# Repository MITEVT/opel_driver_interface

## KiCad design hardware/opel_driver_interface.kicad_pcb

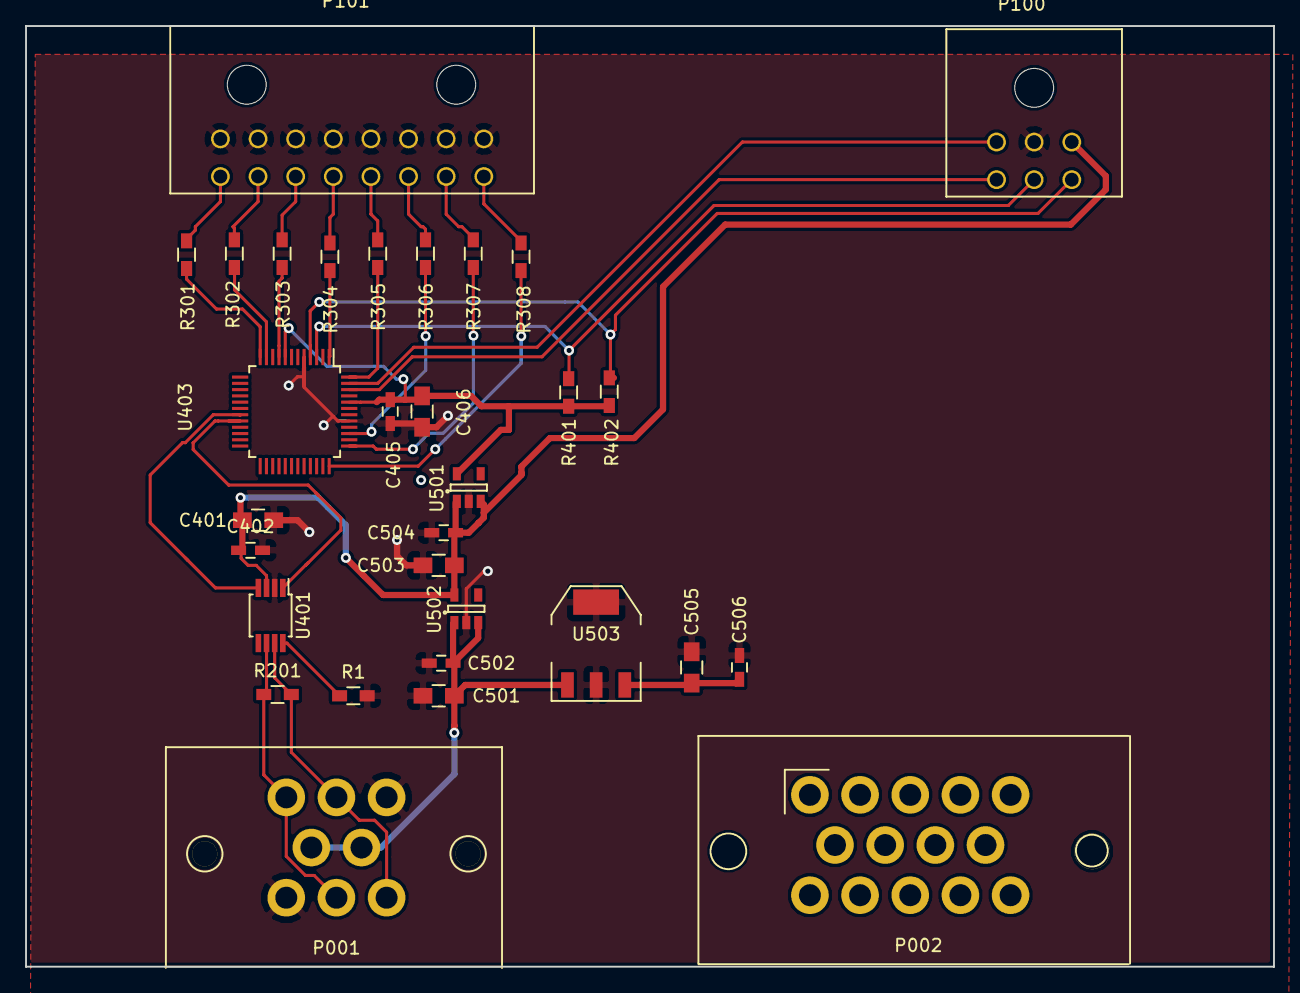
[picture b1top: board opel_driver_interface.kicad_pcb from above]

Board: 2 copper layers, 99.5 x 75.0 mm, 31 parts (0 on the bottom side), 30 nets.

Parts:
C401, C406: 10uF; C_0805_HandSoldering
C402, C405: 0.1uF; C_0603_HandSoldering
C501, C503, C505: 10μ; C_0805_HandSoldering
C502, C504, C506: .1μ; C_0603_HandSoldering
P001: CANCONNECTOR; 776280-1
P002: CONN_01X14; 776267-1
P100: ISP; Connector_Microfit3_Header_02x03_Angled_43045-060x
P101: DEBUG_LED; Connector_Microfit3_Header_02x08_Angled_43045-160x
R1: 20k; R_0603_HandSoldering
R201: R; R_0603_HandSoldering
R301, R302, R303, R304, R305, R306, R307, R308: 100; R_0603_HandSoldering
R401, R402: 10k; R_0603_HandSoldering
U401: MCP2551-I/SN; MSOP-8_3x3mm_Pitch0.65mm
U403: LPC11C14; LQFP-48_7x7mm_Pitch0.5mm
U501: MCP1755-33; SOT-23-5
U502: MCP1755-5; SOT-23-5
U503: Zsr1000gta; SOT-223

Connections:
+3V3: C405.1, C406.1, R401.1, R402.1, U403.8, U403.44, U501.5
+5V: C401.1, C402.1, C503.1, C504.1, P100.3, U401.3, U501.1, U501.3, U502.5
+12V: C501.2, C502.1, P001.4, P001.5, U502.1, U502.3, U503.1
/BACK_PANEL/CANH: P001.2, P001.8, R201.2, U401.7
/BACK_PANEL/CANL: P001.1, P001.7, R201.1, U401.6
/FRONT_PANEL/LED0: R301.1, U403.12
/FRONT_PANEL/LED1: R302.2, U403.11
/FRONT_PANEL/LED2: R303.2, U403.9
/FRONT_PANEL/LED3: R304.1, U403.1
/FRONT_PANEL/LED4: R305.2, U403.48
/FRONT_PANEL/LED5: R306.1, U403.39
/FRONT_PANEL/LED6: R307.2, U403.37
/FRONT_PANEL/LED7: R308.1, U403.36
/FRONT_PANEL/MCU_PROG_N: P100.6, R402.2, U403.4
/FRONT_PANEL/MCU_RESET_N: P100.5, R401.2, U403.3
/FRONT_PANEL/RXD: P100.4, U403.46
/FRONT_PANEL/TXD: P100.1, U403.47
/Micro_Controller/CAN_RXD: U401.4, U403.19
/Micro_Controller/CAN_TXD: U401.1, U403.20
GND: C401.2, C402.2, C405.2, C406.2, C501.1, C502.2, C503.2, C504.2, C505.1, C506.1, P001.3, P001.6, P100.2, P101.1, P101.2, P101.3, P101.4, P101.5, P101.6, P101.7, P101.8, R1.2, U401.2, U403.5, U403.41, U501.2, U502.2, U503.2, U503.4
unnamed: P101.9, R301.2
unnamed: P101.10, R302.1
unnamed: P101.11, R303.1
unnamed: P101.12, R304.2
unnamed: P101.13, R305.1
unnamed: P101.14, R306.2
unnamed: P101.15, R307.1
unnamed: P101.16, R308.2
unnamed: R1.1, U401.8
VCC: C505.2, C506.2, U503.3

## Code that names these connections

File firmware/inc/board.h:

#ifndef __BOARD_H_
#define __BOARD_H_

#include "chip.h"
#include "util.h"
#include <string.h>

// -------------------------------------------------------------
// Global Variables

extern const uint32_t OscRateIn;
volatile uint32_t msTicks; 						// Running count of milliseconds since start

// -------------------------------------------------------------
// Configuration Macros


// -------------------------------------------------------------
// Pin Descriptions

#define LED0_PORT 2
#define LED0_PIN 5

#define LED1_PORT 0
#define LED1_PIN 6

#define LED2_PORT 0
#define LED2_PIN 7

#define LED3_PORT 2
#define LED3_PIN 9

#define UART_RX_PORT 1
#define UART_RX_PIN 6
#define UART_RX_IOCON IOCON_PIO1_6

#define UART_TX_PORT 1
#define UART_TX_PIN 7
#define UART_TX_IOCON IOCON_PIO1_7

// -------------------------------------------------------------
// Computed Macros

#define LED0 LED0_PORT, LED0_PIN
#define LED1 LED1_PORT, LED1_PIN
#define LED2 LED2_PORT, LED2_PIN
#define LED3 LED3_PORT, LED3_PIN

#define UART_RX UART_RX_PORT, UART_RX_PIN
#define UART_TX UART_TX_PORT, UART_TX_PIN

#define Board_LED_On(led) Chip_GPIO_SetPinState(LPC_GPIO, led, true)
#define Board_LED_Off(led) Chip_GPIO_SetPinState(LPC_GPIO, led, false)

// -------------------------------------------------------------
// Board Level Function Prototypes

int8_t Board_SysTick_Init(void);

void Board_LEDs_Init(void);

void Board_UART_Init(uint32_t baudrate);

/**
 * Transmit the given string through the UART peripheral (blocking)
 *
 * @param str pointer to string to transmit
 * @note	This function will send or place all bytes into the transmit
 *			FIFO. This function will block until the last bytes are in the FIFO.
 */
void Board_UART_Print(const char *str);

/**
 * Transmit a string through the UART peripheral and append a newline and a linefeed character (blocking)
 *
 * @param str pointer to string to transmit
 * @note	This function will send or place all bytes into the transmit
 *			FIFO. This function will block until the last bytes are in the FIFO.
 */
void Board_UART_Println(const char *str);

/**
 * Transmit a string containing a number through the UART peripheral (blocking)
 *
 * @param num number to print
 * @param base number base
 * @param crlf append carraige return and line feed
 */
void Board_UART_PrintNum(const int num, uint8_t base, bool crlf);

/**
 * Transmit a byte array through the UART peripheral (blocking)
 *
 * @param	data		: Pointer to data to transmit
 * @param	num_bytes	: Number of bytes to transmit
 * @note	This function will send or place all bytes into the transmit
 *			FIFO. This function will block until the last bytes are in the FIFO.
 */
void Board_UART_SendBlocking(const void *data, uint8_t num_bytes);

/**
 * Read data through the UART peripheral (non-blocking)
 *
 * @param	data		: Pointer to bytes array to fill
 * @param	num_bytes	: Size of the passed data array
 * @return	The actual number of bytes read
 * @note	This function reads data from the receive FIFO until either
 *			all the data has been read or the passed buffer is completely full.
 *			This function will not block. This function ignores errors.
 */
int8_t Board_UART_Read(void *data, uint8_t num_bytes);

void Board_CAN_Init(uint32_t baudrate, void (*rx_callback)(uint8_t), void (*tx_callback)(uint8_t), void (*error_callback)(uint32_t));


#endif

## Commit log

2015-09-19 Initial Tmeplate Commit
2015-09-19 [template] add template for schematics
2015-09-21 Added C gitignore
2015-09-21 Fixed gitignore
2015-09-21 Cleaned up binaries
2015-09-21 Moved over external accessing functions to board file and trting out new test-before-send scheme
2015-09-21 Added README
2015-10-10 cleand repo and removed su files
2015-10-10 Fixed Comments
2015-10-10 Removed Errors
2015-10-24 Made some updates
2015-11-07 add state diagram
2015-11-07 move state diagram
2015-11-07 add new states
2015-11-07 Updating new types.h file
2015-11-07 finish
2015-11-07 Updated types.h
2015-11-07 changed the to da
2015-11-07 replace tabs with spaces
2015-11-14 Added a BLINKER_OFF in the turn_blinker enum
2015-11-14 Added pointers and added blinker struct and headlight struct
2015-11-14 Changed uint8_t switch1 to bool switch1
2015-11-14 Added accessories.c
2015-11-14 Added AccStep, and added variable names to DSM_Step
2015-11-14 Added dsm.c
2015-11-19 changed the inputs to the substate machine
2015-11-19 updated dsm state machine
2015-11-19 Finished half of the code
2015-11-19 added a bit more
2015-11-19 remove swp
2015-11-19 added heartbeat comment
2015-11-19 added init.h
2015-11-19 updated init.c
2015-11-21 fix types.h errors
2015-11-21 fix mode_mode_init
2015-11-21 change fn sigs
2015-11-21 not track vim shit
2015-11-21 progress
2015-11-21 finish accessories
2015-12-05 completed the helper functions
2015-12-05 completed the functions
2015-12-05 created util.h
2015-12-07 changed util.h to DIutil.h
2015-12-07 changed util.c to DIutil.c
2015-12-09 remove util.c
2015-12-09 rename di util
2015-12-09 Actually removed util.h
2015-12-09 changed the name to di_util.h
2015-12-10 added frequencies.h
2015-12-10 added ERROR_HEARTBEAT_LOST
2015-12-10 completed check_validity function
2015-12-10 update accessories fill it in
2015-12-10 added stdint.h
2015-12-10 finish error handling
2015-12-10 changes happened
2015-12-20 fill in main.c with main logic: process input frameworks, error handling, step through DSM, and output
2015-12-20 remove fail state fsm
2015-12-20 add skeletons for sub-FSMs
2016-01-09 updated input struct
2016-01-11 updated the accessories.c code and fixed logical errors
2016-01-11 updated dsm.c
2016-01-11 updated code
2016-01-12 finished init.c, added a counter variable to STATE_T, initialized variables in dsm.c
2016-01-13 inserted the logic for requests and made sure that Shutdown mode only has OFF requests
2016-01-15 removed TODO comment from init.c
2016-01-15 changed last 'else if' statements to 'else' statements at the end of every keymode block
2016-01-15 filled out the output stuff for shutdown.c
2016-01-15 set shutdown.c's acc_out to 'turn_all_off()'
2016-01-15 allowed drive_mode to be 'aux' or 'shutdown_impending'
2016-01-15 changed direction pointer into reg variable ('DRIVE_DIRECTION is an enum, not a struct')
2016-01-15 added comment below the TODO
2016-01-15 added types.h, and finished UART logic for printing out current DSM mode. Also made progress on UART logic on printing out input information
2016-01-16 changed keymodes from pointer to variable (for consistency)
2016-01-16 Finished TODO: for printing out accessory inputs
2016-01-16 added drive direction to States
2016-01-16 implemented direction switching when velocity != 0 and shutdown logic when velocity != 0
2016-01-20 fixed compilation error: OUTPUT_MESSAGES -> OUTPUT_MESSAGES_T
2016-01-20 pushed the pesky Drive direction T enum above everything else
2016-01-20 pushed the out_messages declaration above if else statement
2016-01-20 pushed out_messages delcaration above if else statement
2016-01-22 add types.h
2016-01-22 finish basic util and tests
2016-01-23 finish util processing
2016-01-27 add init outline
2016-01-29 add docs
2016-01-29 added tests of InitStep()
2016-01-30 Fixed documentation problem
    There needs to be two asterisks in the first line of the comment. See commit changes for better detail
2016-01-30 fixed outline and ran it through Eric
2016-01-30 fixed up init psuedocode
2016-01-30 init'd rasp_pi bool to false
2016-01-30 add ui status to inputs heartbeat type
2016-01-30 progress init state machine, add error to types.h
2016-01-30 update types error
2016-01-30 completed a new function (yay)
2016-01-30 updated tests
2016-01-30 finish init.c
2016-02-02 almost working init state machine code
2016-02-03 finish init state machine wahoooo
2016-02-03 add shutdown state; fix init cleanup bug
2016-02-06 fixed function description
2016-02-06 added details and functions to header file
2016-02-06 cleaned up setup
2016-02-06 added DI_NONE to DI_IGNITION
2016-02-06 added DRIVE_NEUTRAL to DRIVE_DIRECTION
2016-02-06 implemented initialize functions
2016-02-06 switched DI_FORWARD to DI_NEUTRAL
2016-02-06 completed asserts for statuses (the TODO) and completed initialize_state() test
2016-02-06 finish shutdown normal state !!!
2016-02-06 add can spec constants
2016-02-10 added units to velocity
2016-02-10 rm'd #include tests.h because it was causing compilation errors and refactored di_util.c to accomodate change from velocity -> velocity_rpm
2016-02-11 cleaned up test folder so that 'make test' compiles! we get A LOT of warnings though
2016-02-13 created test_shutdown_normal.c
2016-02-13 made sure 'make' compiled successfully (sorry for pushing broken code)
2016-02-20 added new ERROR Types, added functions to check Brake value and check velocity_rpm range
2016-02-20 fixed compilation errors
2016-02-20 added brake and throttle value range checks
2016-02-20 add charge design doc
2016-02-20 added function to test to di_util
2016-02-20 added skeleton of charge.c
2016-02-20 added RUN_TEST_GROUP(INIT__TESTS)
2016-02-20 tests pass!! OMG
2016-02-20 working running test file for init.c too!
2016-02-20 yay, everything but the test_init.c runs without compilation errors!
2016-02-20 finish init charge sequence
2016-02-20 add todo with brusa tests
2016-02-21 fix seg fault for init tests
2016-02-21 clean up init tests; tests pass wahoo
2016-03-05 added comments to types.h, and completed charge.c sm
2016-03-05 added new test_charge.c file and set up the initial structs
2016-03-05 huge progress on main()
2016-03-05 add main helpers
2016-03-05 fixed up some compilation errors :("
2016-03-05 remove headlight/brake/wiper control facilities
2016-04-02 created can_spec_constants header file from current can_spec (4/2/2016)
2016-04-09 added led
2016-04-09 adding working led example
2016-04-09 finish bugs flashing lpc
2016-04-30 Updated DI template schematic.
2016-04-30 added an echo to user inputs in main_helpers
2016-05-07 Added relay to DI schematic between power in and power out.
2017-02-04 fix shit
2017-03-04 Updates to test bench configuration
